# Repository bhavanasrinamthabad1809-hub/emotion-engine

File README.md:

## khatak

## My Kathak Emotion Instrument
The idea

I’ve learnt Kathak for a while, and the best part is how a dancer can show a whole emotion with just her face, her hands and her feet. In Indian classical dance those emotions are called the rasas. So I thought: what if I could build a board you play with feelings?

It’s a circuit board shaped like a lotus. Each petal has a button, and each button is one emotion: love (Shringara), courage (Veera), sorrow (Karuna), joy (Hasya) and peace (Shanta). Press one, and an LED behind it lights up in that emotion’s color.

you can select your mood and music plays according to that 

if you see a khatak dancer performing live it is  just completely different world if just feels like divine feminism you could  never get away the eyes 

 i wish i did not stopped  it high school took all my time. 

 here some photos take a moment to watch some khatak reels you will amaze by energy 

## How it works

Pressing a button tells a small chip which emotion I picked. The chip sends a color to the LEDs, and the light travels across the petals like a dancer’s footsteps. That’s tatkar, the stamping rhythm of Kathak. A knob in the corner is my laya control (tempo): turn it one way and the lights get slower (vilambit), the other way and they get faster (drut). In the middle there’s an amber LED called the diya, because every performance starts with lighting a lamp. It flickers like a real flame. Tiny bells (ghungroo) will hang from the petal tips so the board jingles when I move it.

all the switches will play music according to your mood if your mood was sad the music starts from sad takes you into happy with the different  intensity of sound thats how your mood is going to light up as well .

so it plays music according to your mood as some one who loves muscic and dance this is game changer for me 

the dance character is not like that though more art is there just a reference as how i am gonna add ghungro

## What I’m using, and why
## Part	Why
XIAO ESP32-S3	A tiny, cheap brain with built-in USB, so I can program it with one cable
6 SK6812MINI-E LEDs	Each one can show any color, and they chain together on a single wire
12×12 mm tactile buttons with round caps	Small enough for the petals, and the caps look like the buttons in my concept
EC11 rotary encoder	The tempo knob
330 Ω resistors	Protect the first LED’s data pin
100 nF capacitors (1206)	Keep the LEDs’ power steady when they change color
1206 size parts	Big enough for me to solder by hand

## My progress

Schematic: I drew the full circuit in KiCad: five buttons, the encoder, the LED chain, the diya on its own pin, and the capacitors and resistors. ERC came back clean.

PCB: I designed my own lotus outline, placed all the parts in a , and put the LEDs and tiny parts on the back so the front stays clean for art.

Routing: This was the hardest part. I fixed collision errors, deleted old leftover traces, and rotated the XIAO so the USB-C port sits at the edge. At my last check there were about zero connections left.

art time :- added a dancer in middle and showed in images what are the switches did not much more cause i want the main attention to be ghungroo 

## flimware 
going to use circuit board 

wrote the basic coding now cause i dont know how it works will make more changes once it arrives .

## BOM

| Component    | Quantity | Description         | Source                       | Price |
| ------------ | -------: | ------------------- | ---------------------------- | ----: |
| ESP32-S3    |        1 | Microcontroller     |  https://amzn.in/d/0gQRRsHi| $14.75  |
| rotarty encoder |        1 | intensity control       | https://robu.in/product/hongyan-ec11h-7ce20p1zy20-rotary-encoder-with-push-button-switch-vertical-plug-in-5-pin/ | $1.22|
| 330OHM Resistor |        1 | resistor    | https://robu.in/product/330-ohm-1-4w-1206-surface-mount-chip-resistor-pack-of-100/ |$0.10|
| switch  |        5 | User input buttons  | https://amzn.in/d/0ap4lnfj | $3.24 |
| capactior |        6 | release electric enegry   | https://robu.in/product/100nf-1206-surface-mount-multilayer-ceramic-capacitor-pack-of-30/ | $1.26 |
| PCB          |        1 | Custom-designed PCB | [link]https://jlcpcb.com/capabilities/pcb-capabilities| $4|
| knob  |  1 | cap |  https://robu.in/product/potentiometer-knob-rotary-switch-cap-blue-color-pack-of-5-pcs/|$0.31 |
| sk6812 | 8 | leds | [link] |   |

## credits 

all the images credit goes to pin 
and the girls

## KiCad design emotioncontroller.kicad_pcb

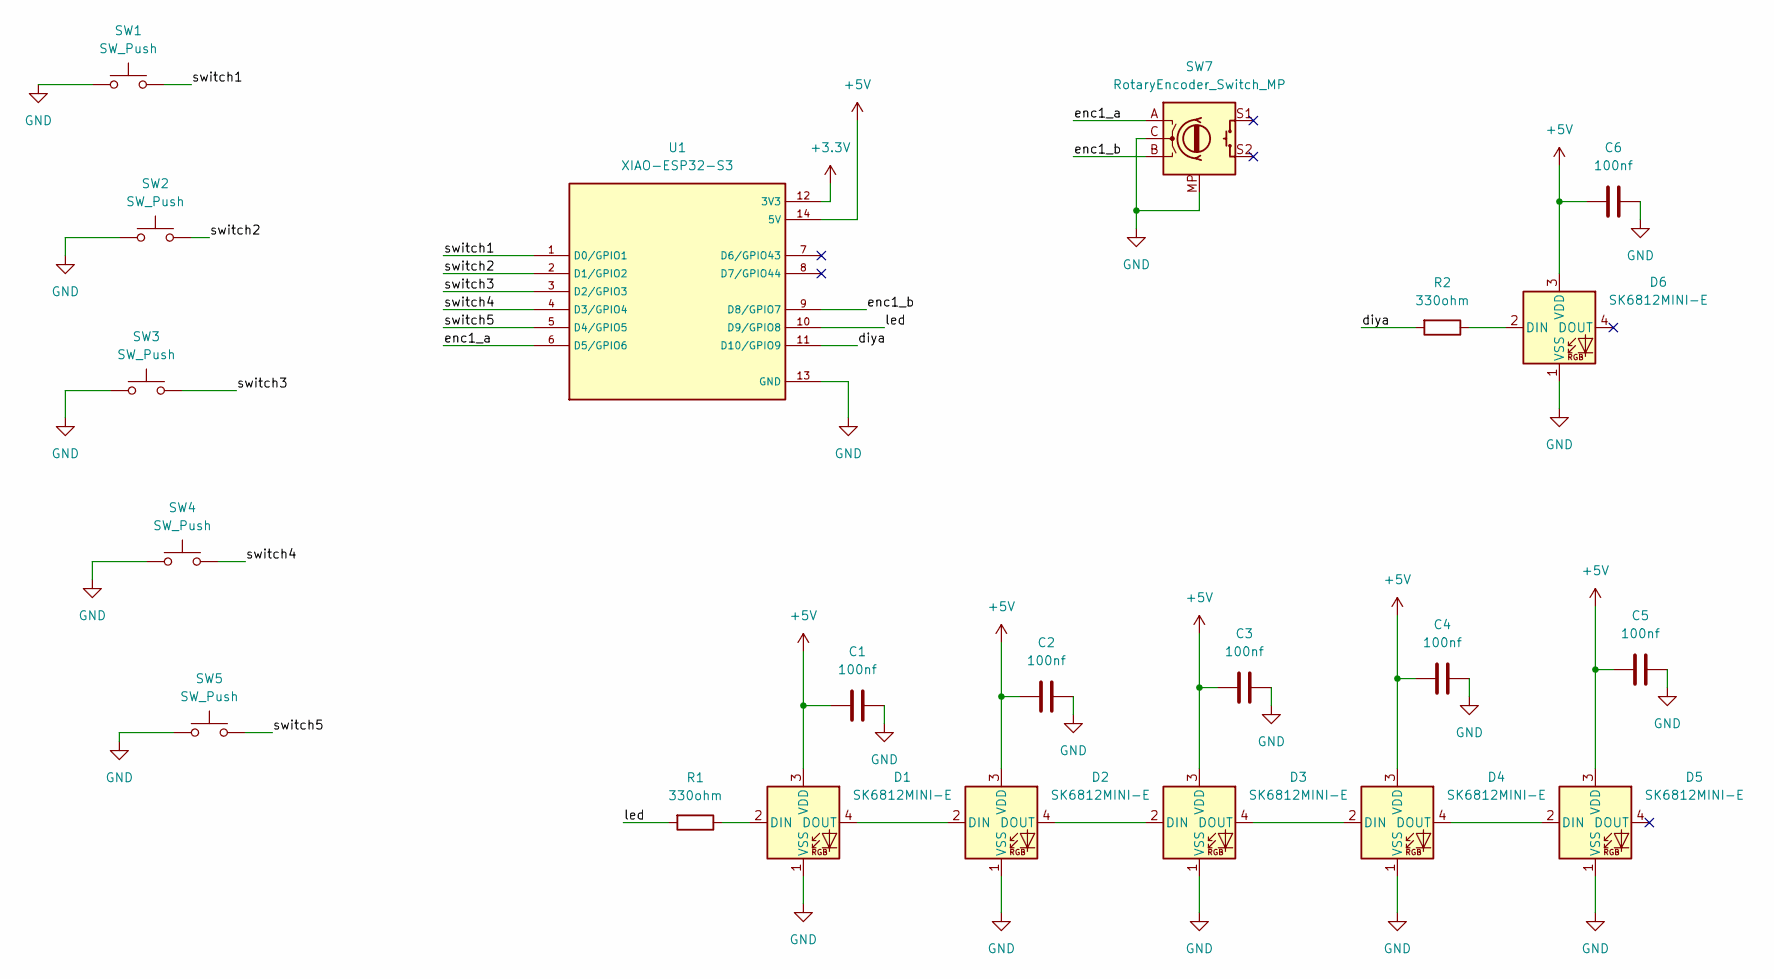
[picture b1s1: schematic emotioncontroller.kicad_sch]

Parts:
C1, C2, C3, C4, C5, C6: 100nf; C_1206_3216Metric
D1, D2, D3, D4, D5, D6: SK6812MINI-E; LED_SK6812MINI-E_3.2x2.8mm_P1.5mm_ReverseMount
R1, R2: 330ohm; R_1206_3216Metric
SW1, SW2, SW3, SW4, SW5: SW_Push; SW_PUSH-12mm
SW7: RotaryEncoder_Switch_MP; RotaryEncoder_Alps_EC11E-Switch_Vertical_H20mm
U1: XIAO-ESP32-S3; XIAO ESP32-S3; PARTREV April 22nd, 2026

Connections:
+3.3V: U1.12 (3V3)
+5V: C1.1, C2.1, C3.1, C4.1, C5.1, C6.1, D1.3 (VDD), D2.3 (VDD), D3.3 (VDD), D4.3 (VDD), D5.3 (VDD), D6.3 (VDD), U1.14 (5V)
/diya: R2.2, U1.11 (D10/GPIO9)
/enc1_a: SW7.A, U1.6 (D5/GPIO6)
/enc1_b: SW7.B, U1.9 (D8/GPIO7)
/led: R1.2, U1.10 (D9/GPIO8)
/switch1: SW1.2, U1.1 (D0/GPIO1)
/switch2: SW2.2, U1.2 (D1/GPIO2)
/switch3: SW3.2, U1.3 (D2/GPIO3)
/switch4: SW4.2, U1.4 (D3/GPIO4)
/switch5: SW5.2, U1.5 (D4/GPIO5)
GND: C1.2, C2.2, C3.2, C4.2, C5.2, C6.2, D1.1 (VSS), D2.1 (VSS), D3.1 (VSS), D4.1 (VSS), D5.1 (VSS), D6.1 (VSS), SW1.1, SW2.1, SW3.1, SW4.1, SW5.1, SW7.C, SW7.MP, U1.13 (GND)
unnamed: D1.2 (DIN), R1.1
unnamed: D1.4 (DOUT), D2.2 (DIN)
unnamed: D2.4 (DOUT), D3.2 (DIN)
unnamed: D3.4 (DOUT), D4.2 (DIN)
unnamed: D4.4 (DOUT), D5.2 (DIN)
unnamed: D6.2 (DIN), R2.1

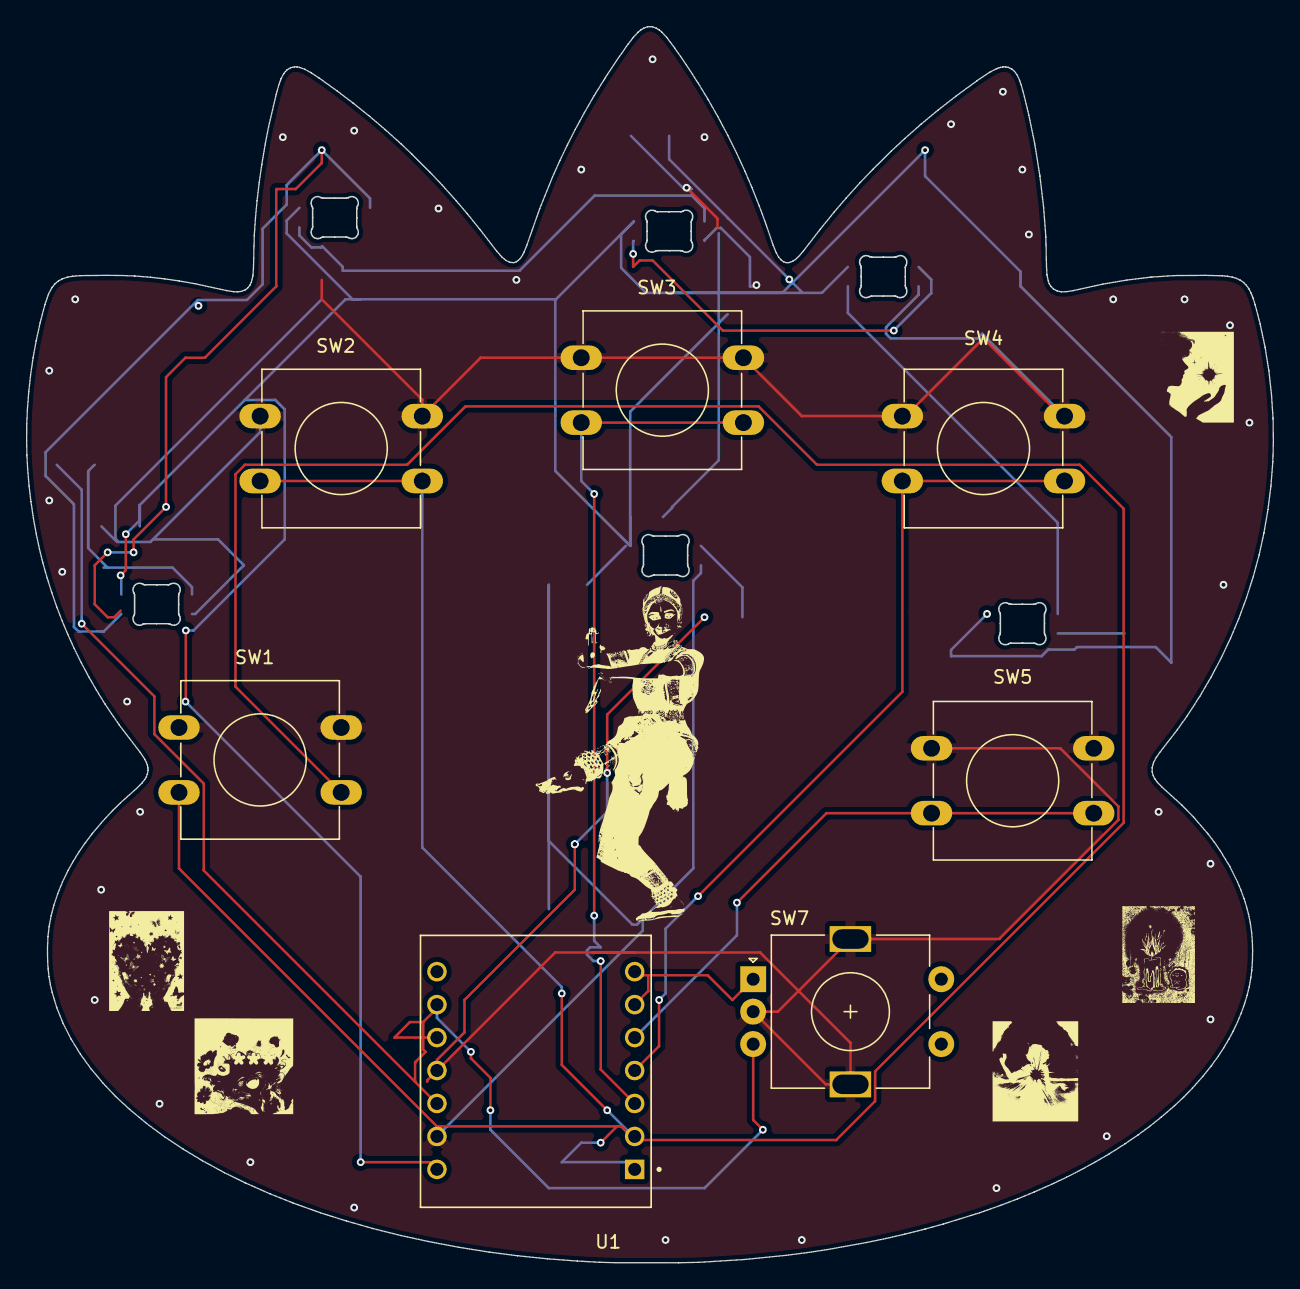
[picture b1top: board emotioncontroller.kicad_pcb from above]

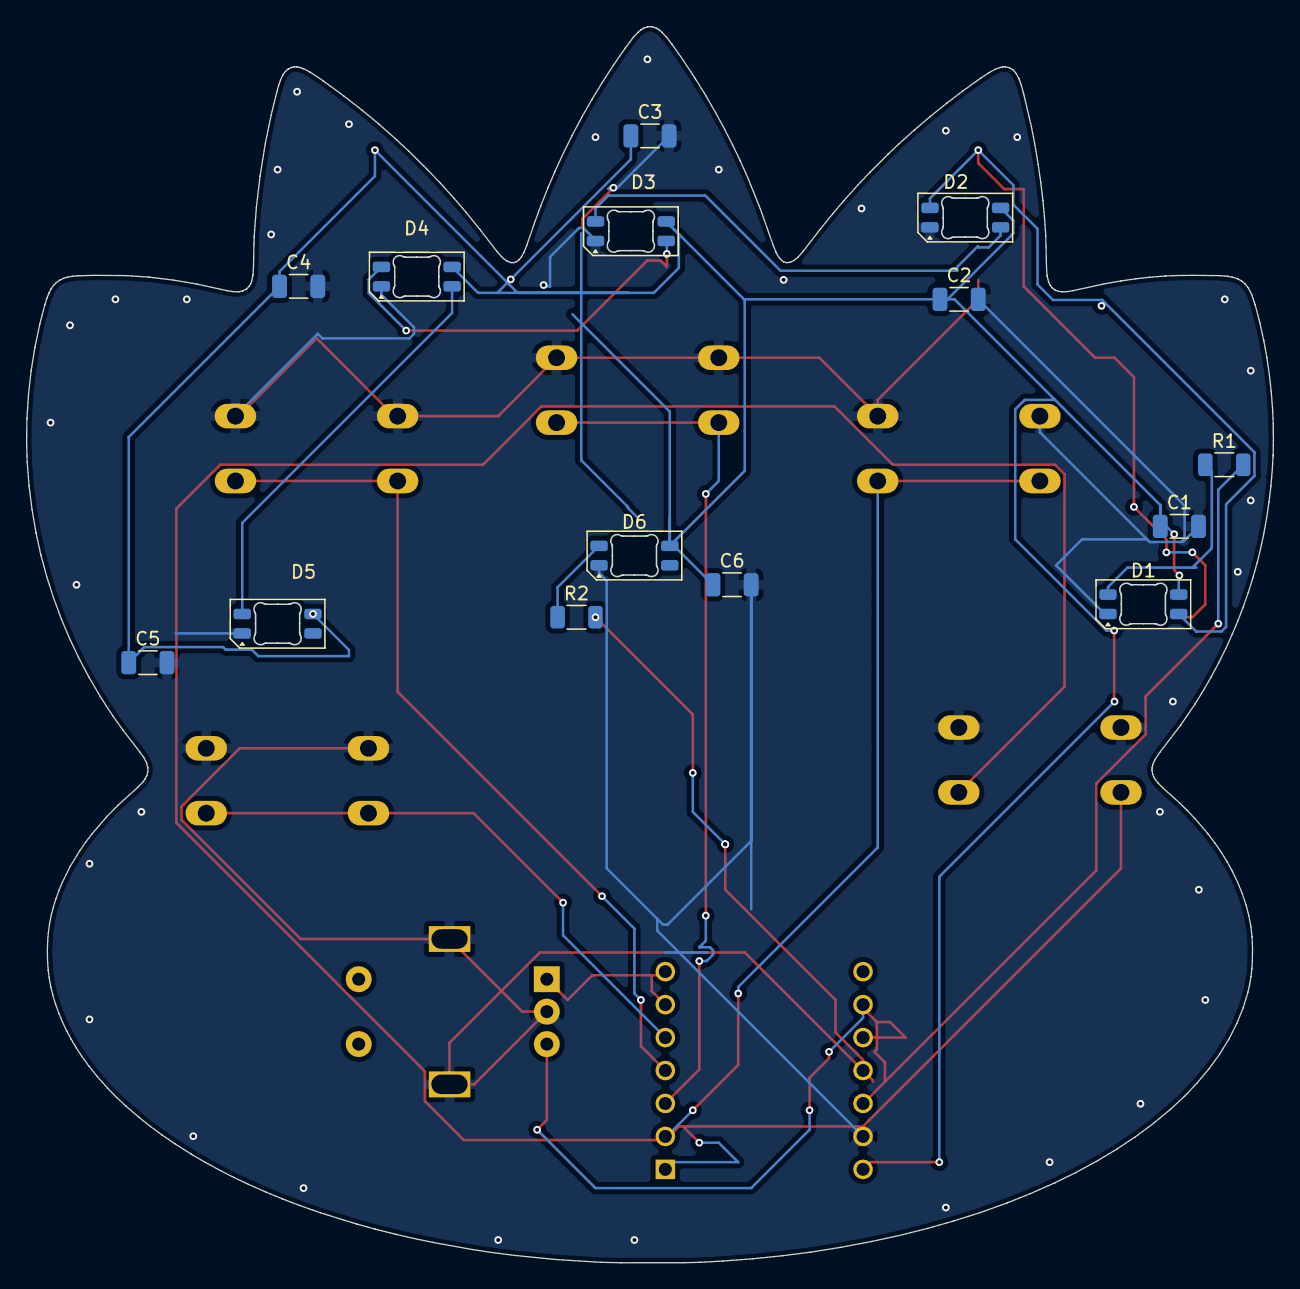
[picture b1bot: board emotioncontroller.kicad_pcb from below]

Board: 2 copper layers, 96.1 x 95.3 mm, 21 parts (14 on the bottom side), 17 nets.

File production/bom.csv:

Designator,Footprint,Quantity,Value,LCSC Part #
"C1, C2, C3, C4, C5, C6",1206,6,100nf,
"D1, D2, D3, D4, D5, D6",LED_SK6812MINI-E_3.2x2.8mm_P1.5mm_ReverseMount,6,SK6812MINI-E,
"R1, R2",1206,2,330ohm,
"SW1, SW2, SW3, SW4, SW5",SW_PUSH-12mm,5,SW_Push,
SW7,RotaryEncoder_Alps_EC11E-Switch_Vertical_H20mm,1,RotaryEncoder_Switch_MP,
U1,XIAO ESP32-S3,1,XIAO-ESP32-S3,
